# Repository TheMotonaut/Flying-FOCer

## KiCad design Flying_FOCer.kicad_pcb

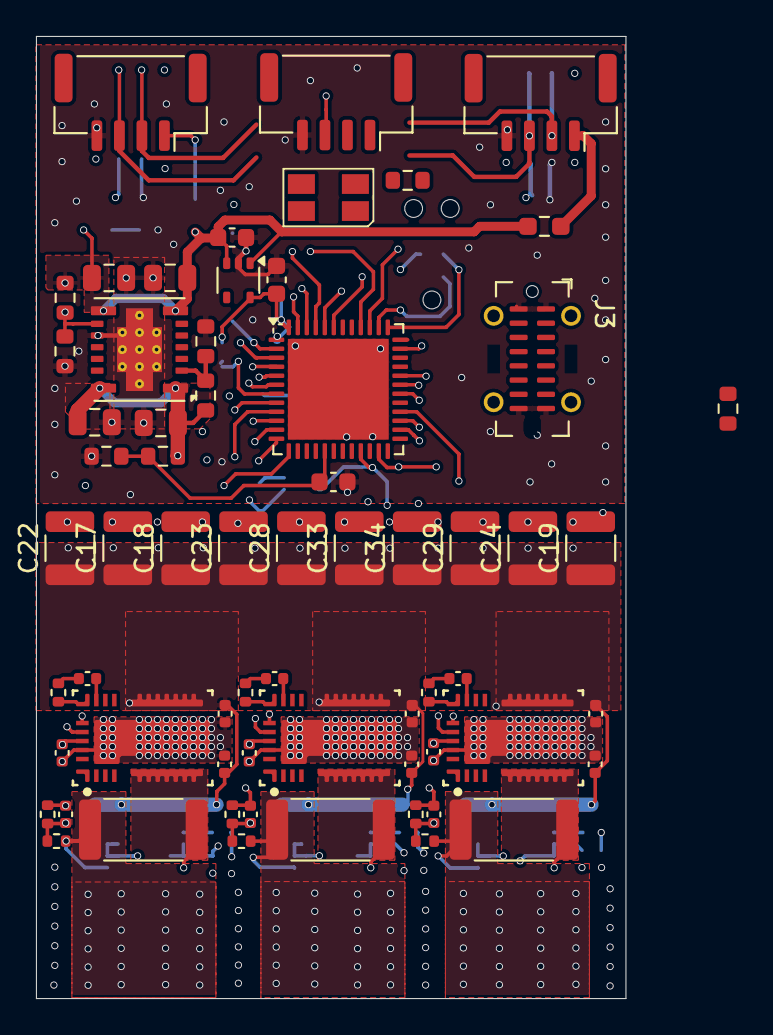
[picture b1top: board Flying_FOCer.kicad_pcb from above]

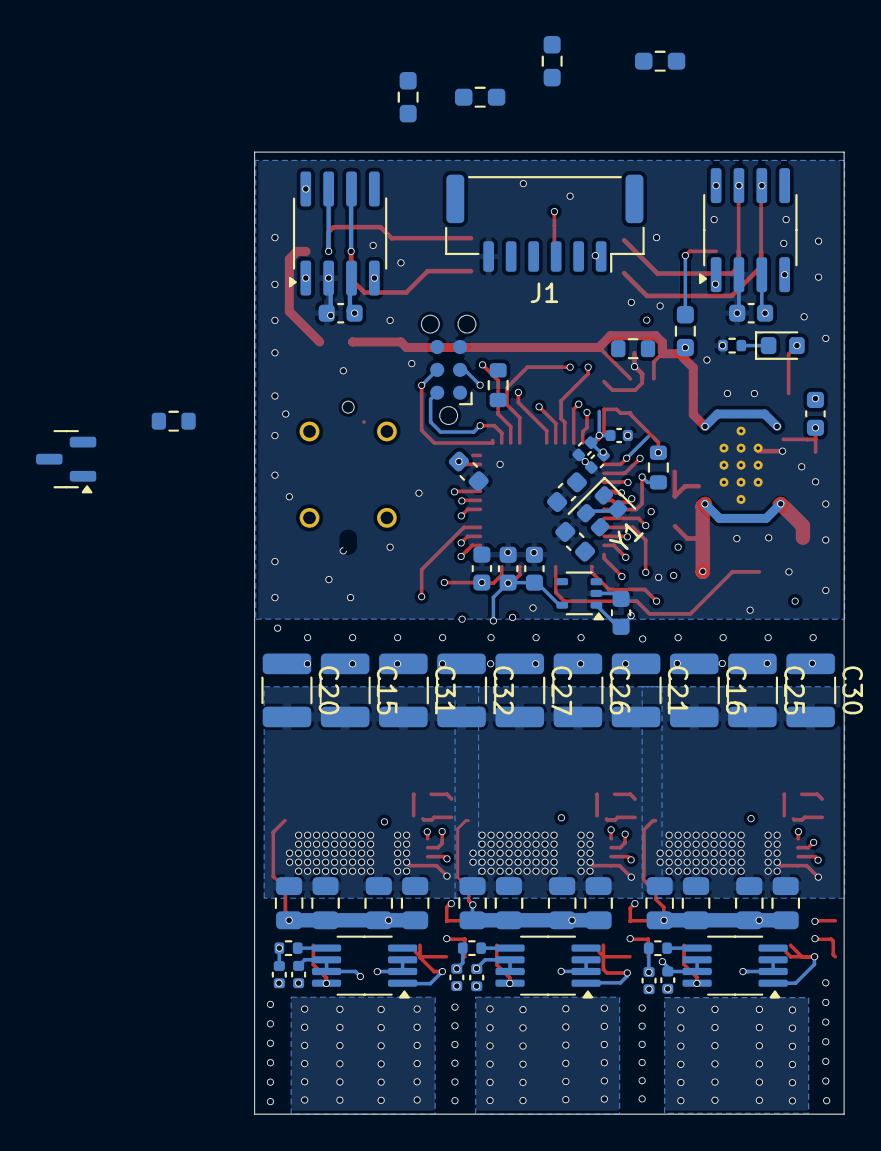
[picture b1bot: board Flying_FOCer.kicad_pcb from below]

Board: 6 copper layers, 32.8 x 53.5 mm, 129 parts (65 on the bottom side), 66 nets.

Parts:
C1, C35, C37, C38: 10p; C_0603_1608Metric
C2, C3: 4u7; C_0805_2012Metric
C4, C5: 22u; C_0805_2012Metric
C6, C7, C8, C9: 1u; C_0603_1608Metric
C10: 1u; C_0402_1005Metric
C11, C14, C41, C42, C47, C48, C51, C52, C53, C58, C59, C62, C63, C64, C69, C70, C73: 100n; C_0402_1005Metric
C12, C13, C36, C39, C40: 100n; C_0603_1608Metric
C15, C16, C17, C18, C19, C20, C21, C22, C23, C24, C25, C26, C27, C28, C29, C30, C31, C32, C33, C34: 10µ; C_1210_3225Metric
C43, C44, C45, C46, C54, C55, C56, C57, C65, C66, C67, C68: 2µ2; C_0805_2012Metric
C49, C60, C71: 2n2; C_0402_1005Metric
C50, C61, C72: 10p; C_0402_1005Metric
D1: LED; LED_0603_1608Metric
D3: D_TVS_Dual_AAC; SOT-23
D4: LED_RAGB; LED_Avago_PLCC4_3.2x2.8mm_CW
J1: Conn_01x06; JST_GH_SM06B-GHS-TB_1x06-1MP_P1.25mm_Horizontal
J2, J5, J6: JST-GH; JST_GH_SM04B-GHS-TB_1x04-1MP_P1.25mm_Horizontal
J3: USB_C_Receptacle_USB2.0_16P; USB_C_Receptacle_G-Switch_GT-USB-7051x
J4: Conn_ARM_SWD_TagConnect_TC2030-NL; Tag-Connect_TC2030-IDC-NL_2x03_P1.27mm_Vertical
R2, R3, R9: 100K; R_0603_1608Metric
R4, R14: 10K; R_0603_1608Metric
R5: 25K; R_0603_1608Metric
R6, R24, R29, R34: 470; R_0402_1005Metric
R7, R8, R10: 5K1; R_0603_1608Metric
R11, R12, R18, R19: 0; R_0603_1608Metric_Pad0.98x0.95mm_HandSolder
R13: 470; R_0603_1608Metric
R15, R16: 220; R_0603_1608Metric
R17, R20: 120; R_0603_1608Metric_Pad0.98x0.95mm_HandSolder
R21, R26, R31: 2R2; R_0402_1005Metric
R22, R27, R32: 500µ; R_2512_6332Metric
R23, R28, R33: 100K; R_0402_1005Metric
R25, R30, R35: 5K1; R_0402_1005Metric
U1: TPSM5601; Texas_B3QFN-14-1EP_5x5.5mm_P0.65mm_ThermalVia
U2, U3: TLV70033_SOT353; SOT-353_SC-70-5
U4: STM32G474CEUx; QFN-48-1EP_7x7mm_P0.5mm_EP5.6x5.6mm
U5, U7: TCAN3414; SOIC-8_3.9x4.9mm_P1.27mm
U8, U10, U12: LMG2100R026VBNR; VBN0018A-MFG
U9, U11, U13: AD8417; MSOP-8_3x3mm_P0.65mm
Y1: 32MHz; Crystal_SMD_2016-4Pin_2.0x1.6mm

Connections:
+3v3: C7.2, C10.1, C11.1, C12.1, C13.1, C14.1, C39.1, C40.1, D4.2 (A), R14.2, U2.5 (OUT), U4.1 (VBAT), U4.23 (VDD), U4.35 (VDD), U4.48 (VDD), U5.3 (VCC), U7.3 (VCC)
+3v3A: C9.2, C36.1, C51.1, C62.1, C73.1, U3.5 (OUT), U4.21 (VDDA), U9.6 (VS), U9.7 (REF1), U11.6 (VS), U11.7 (REF1), U13.6 (VS), U13.7 (REF1)
+5V: C1.1, C4.2, C5.2, C6.2, C8.2, C47.1, C58.1, C69.1, D1.2 (A), R3.2, R11.1, R12.1, U1.7 (VOUT), U1.8 (VOUT), U2.1 (IN), U2.3 (EN), U3.1 (IN), U3.3 (EN), U8.14 (VDD), U10.14 (VDD), U12.14 (VDD)
+5VCAN1: J5.1, R11.2
+5VCAN2: J6.1, R12.2
+BATT: C2.2, C3.2, C15.1, C16.1, C17.1, C18.1, C19.1, C20.1, C21.1, C22.1, C23.1, C24.1, C25.1, C26.1, C27.1, C28.1, C29.1, C30.1, C31.1, C32.1, C33.1, C34.1, C41.1, C42.1, C43.1, C44.1, C45.1, C46.1, C52.1, C53.1, C54.1, C55.1, C56.1, C57.1, C63.1, C64.1, C65.1, C66.1, C67.1, C68.1, R2.2, R9.1, U1.1 (VIN), U1.14 (VIN), U8.7 (VIN), U10.7 (VIN), U12.7 (VIN)
/CAN1_N: J5.3, R17.2, R18.1, U5.6 (CANL)
/CAN1_P: J5.2, R17.1, R19.2, U5.7 (CANH)
/CAN1_RX: U4.46 (PB8), U5.4 (RXD)
/CAN1_TX: U4.47 (PB9), U5.1 (TXD)
/CAN2_N: J6.3, R18.2, R20.1, U7.6 (CANL)
/CAN2_P: J6.2, R19.1, R20.2, U7.7 (CANH)
/CAN2_RX: U4.43 (PB5), U7.4 (RXD)
/CAN2_TX: U4.44 (PB6), U7.1 (TXD)
/CURR_SENS_U: C49.1, R24.2, U4.13 (PA5)
/CURR_SENS_V: C60.1, R29.2, U4.12 (PA4)
/CURR_SENS_W: C71.1, R34.2, U4.11 (PA3)
/PWM_HIGH_U: U4.30 (PA8), U8.12 (HI)
/PWM_HIGH_V: U4.31 (PA9), U10.12 (HI)
/PWM_HIGH_W: U4.32 (PA10), U12.12 (HI)
/PWM_LOW_U: U4.26 (PB13), U8.13 (LI)
/PWM_LOW_V: U4.27 (PB14), U10.13 (LI)
/PWM_LOW_W: U4.28 (PB15), U12.13 (LI)
/Power Stage U/SW: R22.2, R23.2, U9.1 (IN-)
/Power Stage V/SW: R27.2, R28.2, U11.1 (IN-)
/Power Stage W/SW: R32.2, R33.2, U13.1 (IN-)
/STB_CAN1: U4.40 (PC11), U5.8 (STB)
/STB_CAN2: U4.39 (PC10), U7.8 (STB)
/SWCLK: J4.4 (SWCLK), U4.37 (PA14)
/SWDIO: J4.2 (SWDIO), U4.38 (PA15)
/USB_N: D3.2 (A2), J3.A7 (D-), J3.B7 (D-), U4.33 (PA11)
/USB_P: D3.1 (A1), J3.A6 (D+), J3.B6 (D+), U4.34 (PA12)
/VBUS_SENS: C35.1, R9.2, R10.2, U4.17 (PB0)
/VOLT_SENS_U: C50.1, R23.1, R25.2, U4.10 (PA2)
/VOLT_SENS_V: C61.1, R28.1, R30.2, U4.9 (PA1)
/VOLT_SENS_W: C72.1, R33.1, R35.2, U4.8 (PA0)
/~RST: J4.3 (~RESET), R14.1, U4.7 (PG10)
GND: C2.1, C3.1, C4.1, C5.1, C6.1, C7.1, C8.1, C9.1, C10.2, C11.2, C12.2, C13.2, C14.2, C15.2, C16.2, C17.2, C18.2, C19.2, C20.2, C21.2, C22.2, C23.2, C24.2, C25.2, C26.2, C27.2, C28.2, C29.2, C30.2, C31.2, C32.2, C33.2, C34.2, C35.2, C36.2, C37.2, C38.1, C39.2, C40.2, C41.2, C42.2, C43.2, C44.2, C45.2, C46.2, C47.2, C49.2, C50.2, C51.2, C52.2, C53.2, C54.2, C55.2, C56.2, C57.2, C58.2, C60.2, C61.2, C62.2, C63.2, C64.2, C65.2, C66.2, C67.2, C68.2, C69.2, C71.2, C72.2, C73.2, D3.3 (common), J1.6, J2.4, J3.A1 (GND), J3.A12 (GND), J3.B1 (GND), J3.B12 (GND), J4.5 (GND), J5.4, J6.4, R4.1, R5.1, R6.1, R7.1, R8.1, R10.1, R25.1, R30.1, R35.1, U1.10 (AGND), U1.15 (PGND), U2.2 (GND), U3.2 (GND), U4.49 (VSS), U5.2 (GND), U7.2 (GND), U8.6 (PGND), U8.15 (DGND), U9.2 (GND), U9.3 (REF2), U10.6 (PGND), U10.15 (DGND), U11.2 (GND), U11.3 (REF2), U12.6 (PGND), U12.15 (DGND), U13.2 (GND), U13.3 (REF2), Y1.2, Y1.4
unnamed: C48.1, R21.1
unnamed: C59.1, R26.1
unnamed: C70.1, R31.1
unnamed: D1.1 (K), R6.2
unnamed: D4.4 (BK), R16.1
unnamed: D4.3 (GK), R15.1
unnamed: D4.1 (RK), R13.1
unnamed: J3.A5 (CC1), R8.2
unnamed: J3.B5 (CC2), R7.2
unnamed: R2.1, R4.2, U1.2 (EN)
unnamed: C1.2, R3.1, R5.2, U1.9 (FB)
unnamed: R13.2, U4.2 (PC13)
unnamed: R15.2, U4.3 (PC14)
unnamed: R16.2, U4.4 (PC15)
unnamed: C37.1, U4.5 (PF0), Y1.3
unnamed: C38.2, U4.6 (PF1), Y1.1
unnamed: C48.2, U8.10 (HB)
unnamed: R21.2, U8.11 (HS)
unnamed: R22.1, U8.5 (SW), U9.8 (IN+)
unnamed: R24.1, U9.5 (OUT)
unnamed: C59.2, U10.10 (HB)
unnamed: R26.2, U10.11 (HS)
unnamed: R27.1, U10.5 (SW), U11.8 (IN+)
unnamed: R29.1, U11.5 (OUT)
unnamed: C70.2, U12.10 (HB)
unnamed: R31.2, U12.11 (HS)
unnamed: R32.1, U12.5 (SW), U13.8 (IN+)
unnamed: R34.1, U13.5 (OUT)

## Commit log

2026-01-11 Init, version 3
2026-03-26 Changed Lib link and added BGA part
